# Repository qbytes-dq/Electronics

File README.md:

# Electronics

Electronic projects.

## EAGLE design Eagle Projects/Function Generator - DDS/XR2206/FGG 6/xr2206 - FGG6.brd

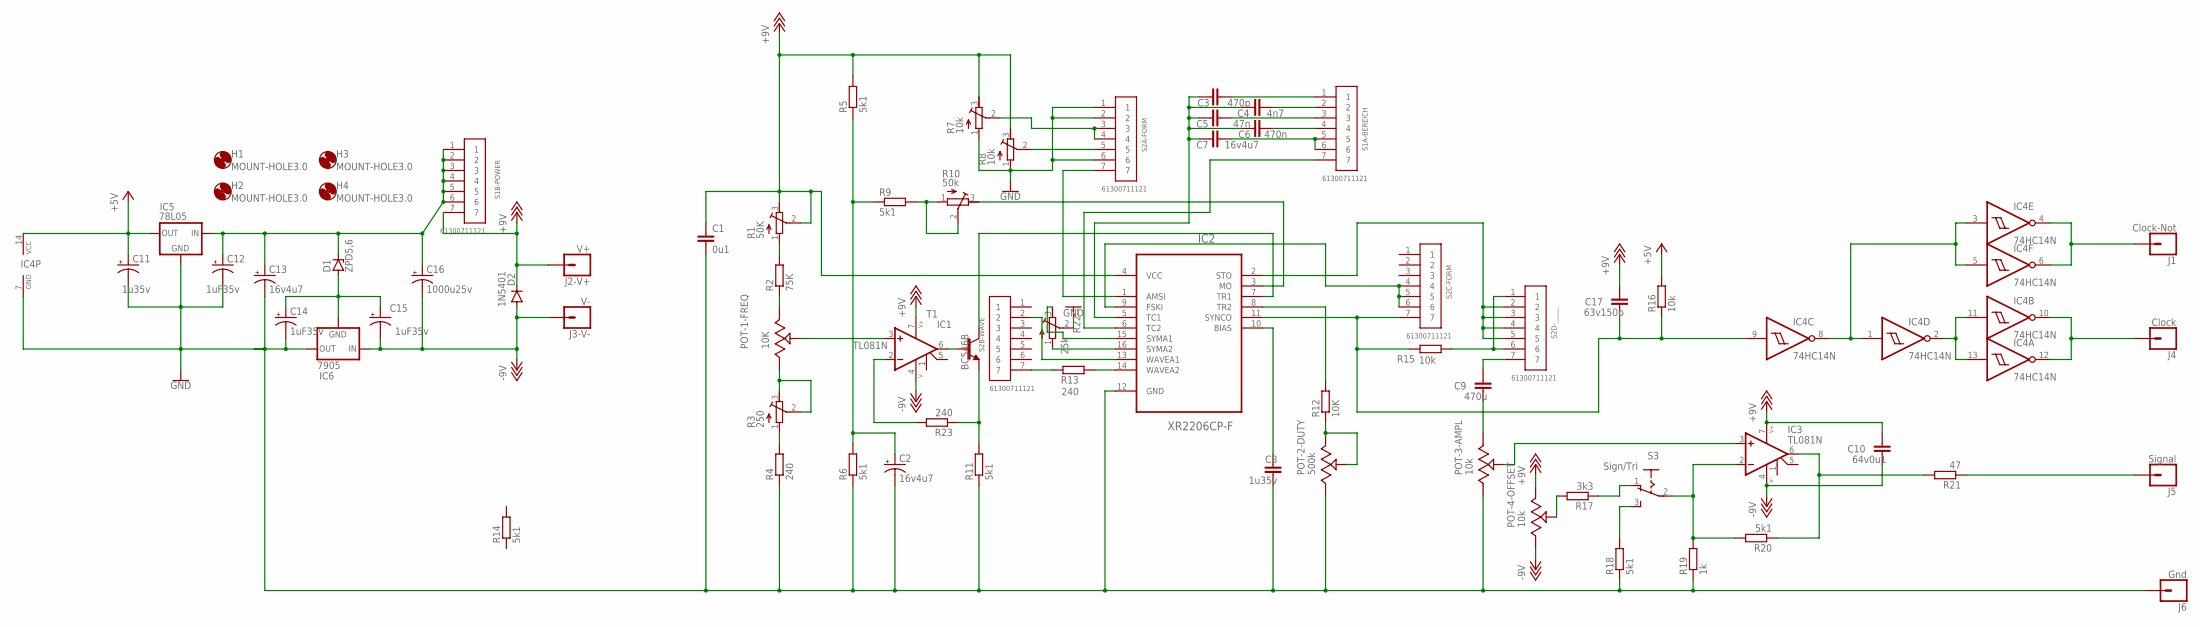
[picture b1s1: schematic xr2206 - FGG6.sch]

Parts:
C1: 0u1; CAP-PTH-10MM
C2: 16v4u7; CPOL-RADIAL-5MM-10MM-KIT
C3: 470p; CAP-PTH-10MM
C4: 4n7; CAP-PTH-10MM
C5: 47n; CAP-PTH-10MM
C6: 470n; CAP-PTH-10MM
C7: 16v4u7; CAP-PTH-10MM
C8: 1u35v; CAP-PTH-10MM
C9: 470u; CAP-PTH-10MM
C10: 64v0u1; CAP-PTH-10MM
C11: 1u35v; CPOL-RADIAL-2.5MM-5MM
C12, C14, C15: 1uF35v; CPOL-RADIAL-2.5MM-5MM
C13: 16v4u7; CPOL-RADIAL-2.5MM-5MM
C16: 1000u25v; CPOL-RADIAL-5MM-10MM-KIT
C17: 63v150p; CAP-PTH-10MM
D1: ZPD5,6; C1702-15
D2: 1N5401; DO201-15
H1, H2, H3, H4: MOUNT-HOLE3.0; 3,0
IC1, IC3: TL081N; DIL08
IC2: XR2206CP-F; DIP254P762X533-16
IC4: 74HC14N; DIL14
IC5: 78L05; 78XXL
IC6: 7905; 79XXL
J1: Clock-Not; 1X01
J2-V+: V+; 1X01
J3-V-: V-; 1X01
J4: Clock; 1X01
J5: Signal; 1X01
J6: Gnd; 1X01
POT-1-FREQ: 10K; 3310C-001-503L
POT-2-DUTY: 500k; 3310C-001-503L
POT-3-AMPL, POT-4-OFFSET: 10k; 3310C-001-503L
R1: 50K; RTRIM64W
R2: 75K; 0207/12
R3: 250; RTRIM64W
R4, R13: 240; 0207/7
R5, R6, R11, R14, R18, R20: 5k1; 0207/7
R7, R8: 10k; RTRIM64W
R9: 5k1; 0207/12
R10: 50k; RTRIM64W
R12: 10K; 0207/12
R15, R16: 10k; 0207/7
R17: 3k3; 0207/12
R19: 1k; 0207/7
R21: 47; 0207/7
R22---: 25k; RTRIM64W
R23: 240; 0207/12
S1A-BEREICH, S1B-POWER, S2A-FORM, S2B-WAVE, S2C-FORM, S2D-_____: 61300711121
S3: Sign/Tri; 255SB
T1: BC546B; TO92-EBC

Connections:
+5V: C11.1 (+), IC4.14 (VCC), IC5.OUT, R16.2
+18V: C1.1, C10.2, C17.2, D2.C, IC1.7 (V+), IC2.4 (VCC), IC3.7 (V+), J2-V+.1, POT-4-OFFSET.1, R1.2 (S), R1.3 (E), R5.2, R7.3 (E), R8.3 (E), S1B-POWER.7
-18V: C10.1, C15.2 (-), C16.-, D2.A, IC1.4 (V-), IC3.4 (V-), IC6.IN, J3-V-.1, POT-4-OFFSET.3
GND: C1.2, C2.-, C8.1, C11.2 (-), C12.2 (-), C13.2 (-), C14.2 (-), IC2.12 (GND), IC4.7 (GND), IC5.GND, IC6.OUT, J6.1, POT-2-DUTY.3, POT-3-AMPL.3, R4.1, R6.1, R7.1 (A), R8.1 (A), R11.1, R18.1, R19.1, R22---.2 (S), S2A-FORM.1, S2A-FORM.2, S2A-FORM.6
unnamed: R3.1 (A), R4.2
unnamed: POT-1-FREQ.3, R3.2 (S), R3.3 (E)
unnamed: POT-1-FREQ.1, R2.1
unnamed: R1.1 (A), R2.2
unnamed: C12.1 (+), C13.1 (+), C16.+, D1.C, IC5.IN, S1B-POWER.1, S1B-POWER.2, S1B-POWER.3, S1B-POWER.4, S1B-POWER.5, S1B-POWER.6
unnamed: C14.1 (+), C15.1 (+), D1.A, IC6.GND
unnamed: IC1.3 (+IN), POT-1-FREQ.2
unnamed: IC1.6 (OUT), T1.B
unnamed: IC1.2 (-IN), R23.2
unnamed: R11.2, R23.1, T1.E
unnamed: IC2.7 (TR1), T1.C
unnamed: C2.+, R5.1, R6.2, R9.1
unnamed: R9.2, R10.1 (A), R10.2 (S)
unnamed: IC2.3 (MO), R10.3 (E)
unnamed: IC2.8 (TR2), R12.2
unnamed: POT-2-DUTY.1, POT-2-DUTY.2, R12.1
unnamed: IC2.1 (AMSI), S2A-FORM.7
unnamed: R8.2 (S), S2A-FORM.5
unnamed: R7.2 (S), S2A-FORM.3, S2A-FORM.4
unnamed: IC2.13 (WAVEA1), S2B-WAVE.2
unnamed: R13.2, S2B-WAVE.7
unnamed: IC2.14 (WAVEA2), R13.1
unnamed: IC2.6 (TC2), S1A-BEREICH.7
unnamed: C3.1, C4.1, C5.1, C6.1, C7.1, IC2.5 (TC1)
unnamed: C3.2, S1A-BEREICH.1
unnamed: C4.2, S1A-BEREICH.2
unnamed: C6.2, S1A-BEREICH.4
unnamed: C5.2, S1A-BEREICH.3
unnamed: C7.2, S1A-BEREICH.5, S1A-BEREICH.6
unnamed: C8.2, IC2.10 (BIAS)
unnamed: IC2.9 (FSKI), S2C-FORM.4, S2C-FORM.5, S2C-FORM.6
unnamed: C17.1, IC2.11 (SYNCO), IC4.9 (I), R15.2, R16.1, S2C-FORM.7
unnamed: IC2.2 (STO), S2D-_____.2, S2D-_____.3, S2D-_____.4, S2D-_____.5
unnamed: IC4.1 (I), IC4.3 (I), IC4.5 (I), IC4.8 (O)
unnamed: IC4.2 (O), IC4.11 (I), IC4.13 (I)
unnamed: IC4.10 (O), IC4.12 (O), J4.1
unnamed: R15.1, S2D-_____.1, S2D-_____.6
unnamed: IC3.3 (+IN), POT-3-AMPL.2
unnamed: IC4.4 (O), IC4.6 (O), J1.1
unnamed: C9.2, S2D-_____.7
unnamed: C9.1, POT-3-AMPL.1
unnamed: POT-4-OFFSET.2, R17.2
unnamed: R17.1, S3.1 (O)
unnamed: IC3.2 (-IN), R19.2, R20.2, S3.2
unnamed: R18.2, S3.3 (S)
unnamed: IC3.6 (OUT), R20.1, R21.2
unnamed: J5.1, R21.1
unnamed: IC2.16 (SYMA2), R22---.1 (A)
unnamed: IC2.15 (SYMA1), R22---.3 (E)

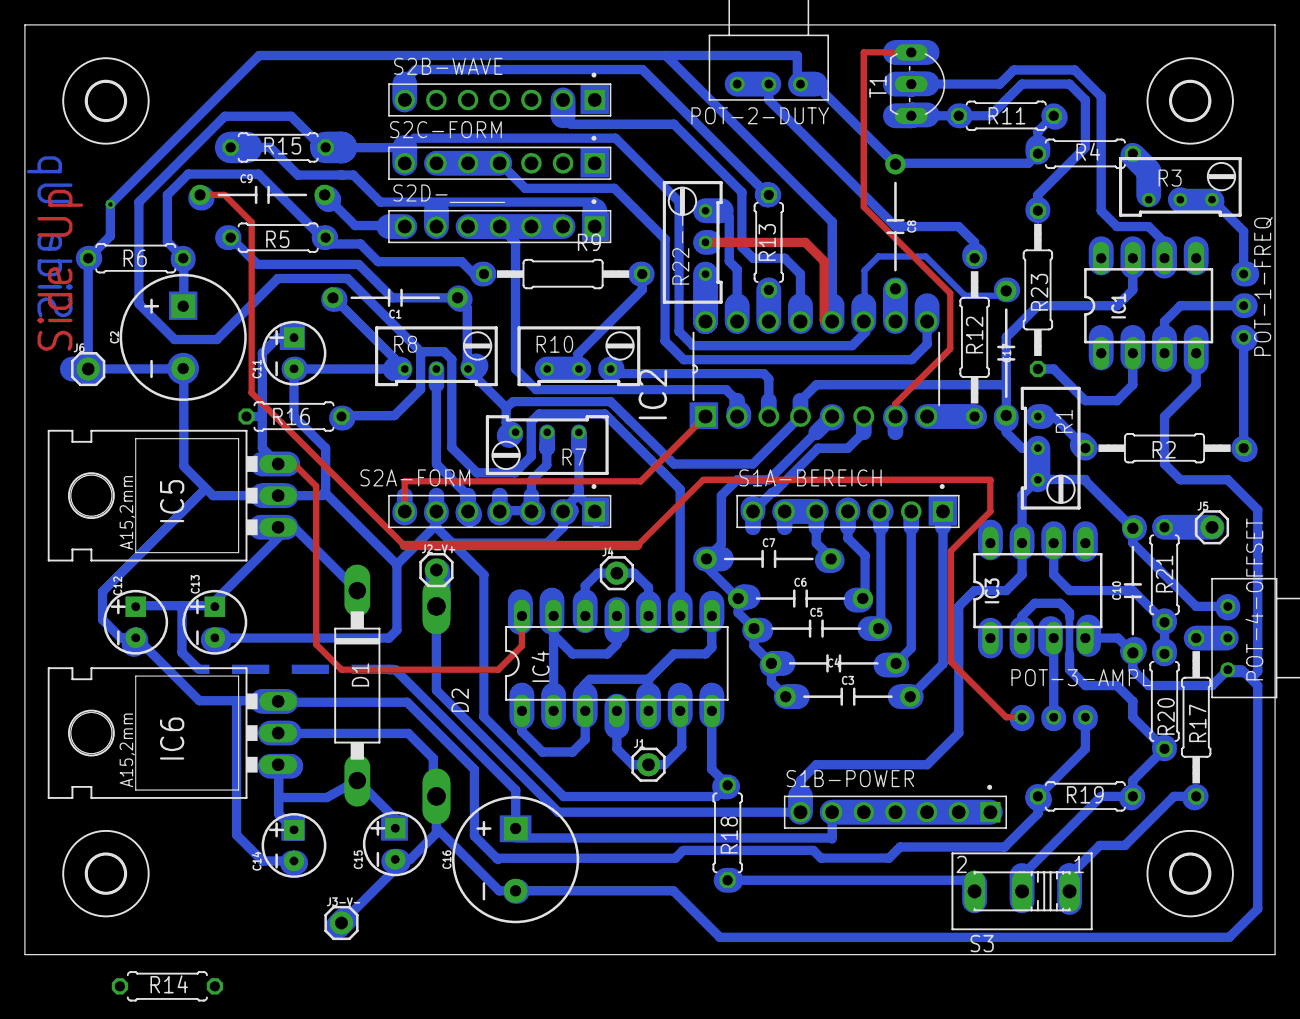
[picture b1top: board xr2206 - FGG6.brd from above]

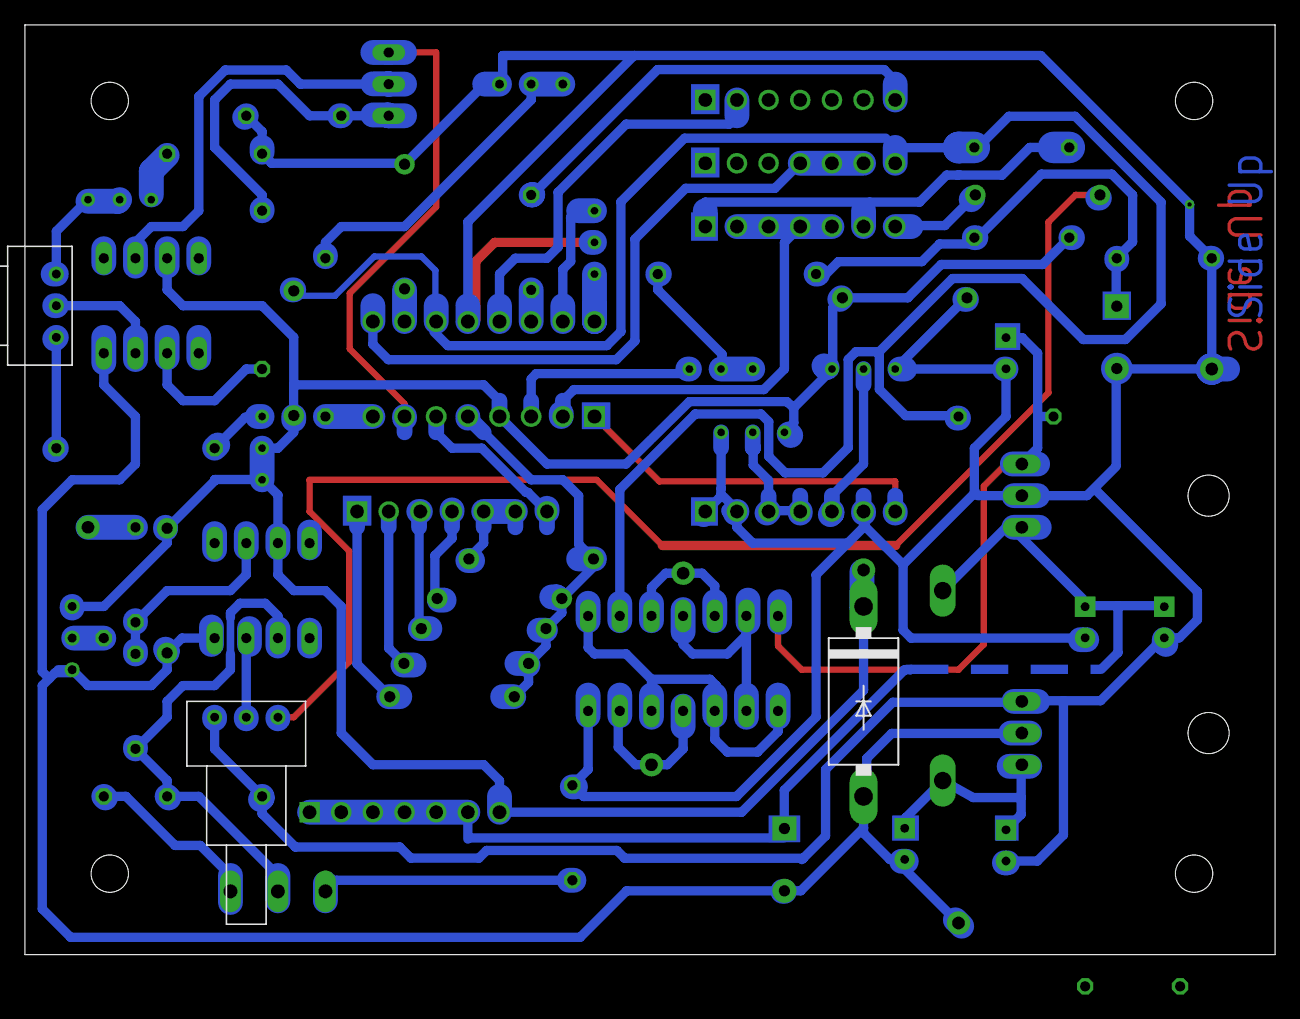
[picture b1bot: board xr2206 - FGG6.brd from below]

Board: 2 copper layers, 100.3 x 74.6 mm, 70 parts (3 on the bottom side), 53 nets.

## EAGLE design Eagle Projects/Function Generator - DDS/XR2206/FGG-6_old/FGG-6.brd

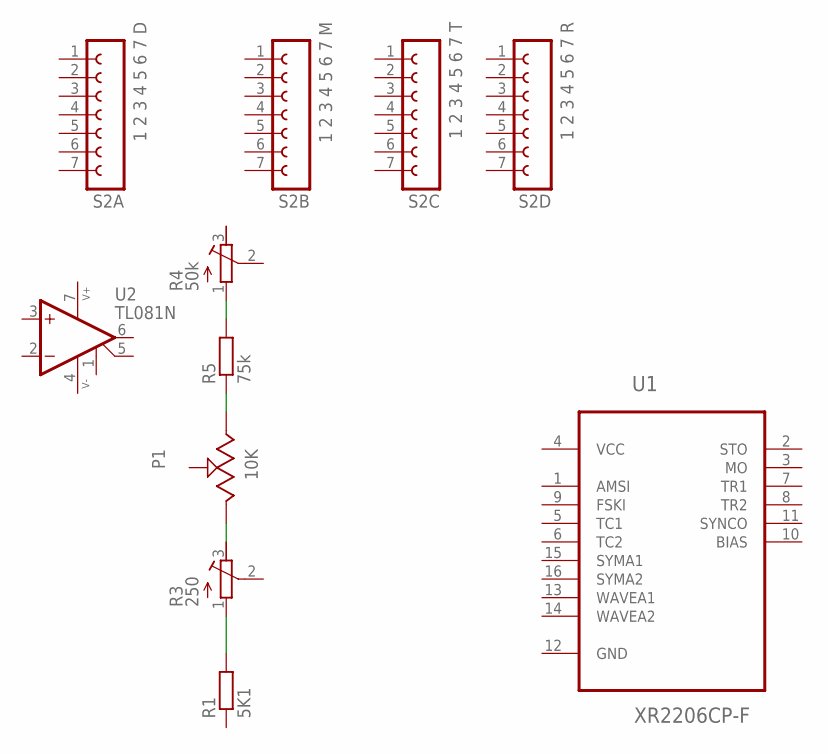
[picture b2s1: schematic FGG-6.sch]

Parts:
P1: 10K; 91A1A-B28-B15L-ND
R1: 5K1; 0207/10
R3: 250; RTRIM64W
R4: 50k; RTRIM64W
R5: 75k; 0207/10
S2A: 1 2 3 4 5 6 7 D; FE07
S2B: 1 2 3 4 5 6 7 M; FE07
S2C: 1 2 3 4 5 6 7 T; FE07
S2D: 1 2 3 4 5 6 7 R; FE07
U1: XR2206CP-F; DIP254P762X533-16
U2: TL081N; DIL08

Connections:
unnamed: R1.2, R3.1 (A)
unnamed: P1.1, R3.3 (E)
unnamed: P1.3, R5.1
unnamed: R4.1 (A), R5.2
V+: U2.7 (V+)
V-: U2.4 (V-)
VCC: U1.4 (VCC)

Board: 2 copper layers, 11 parts (0 on the bottom side), 4 nets, no tracks yet.

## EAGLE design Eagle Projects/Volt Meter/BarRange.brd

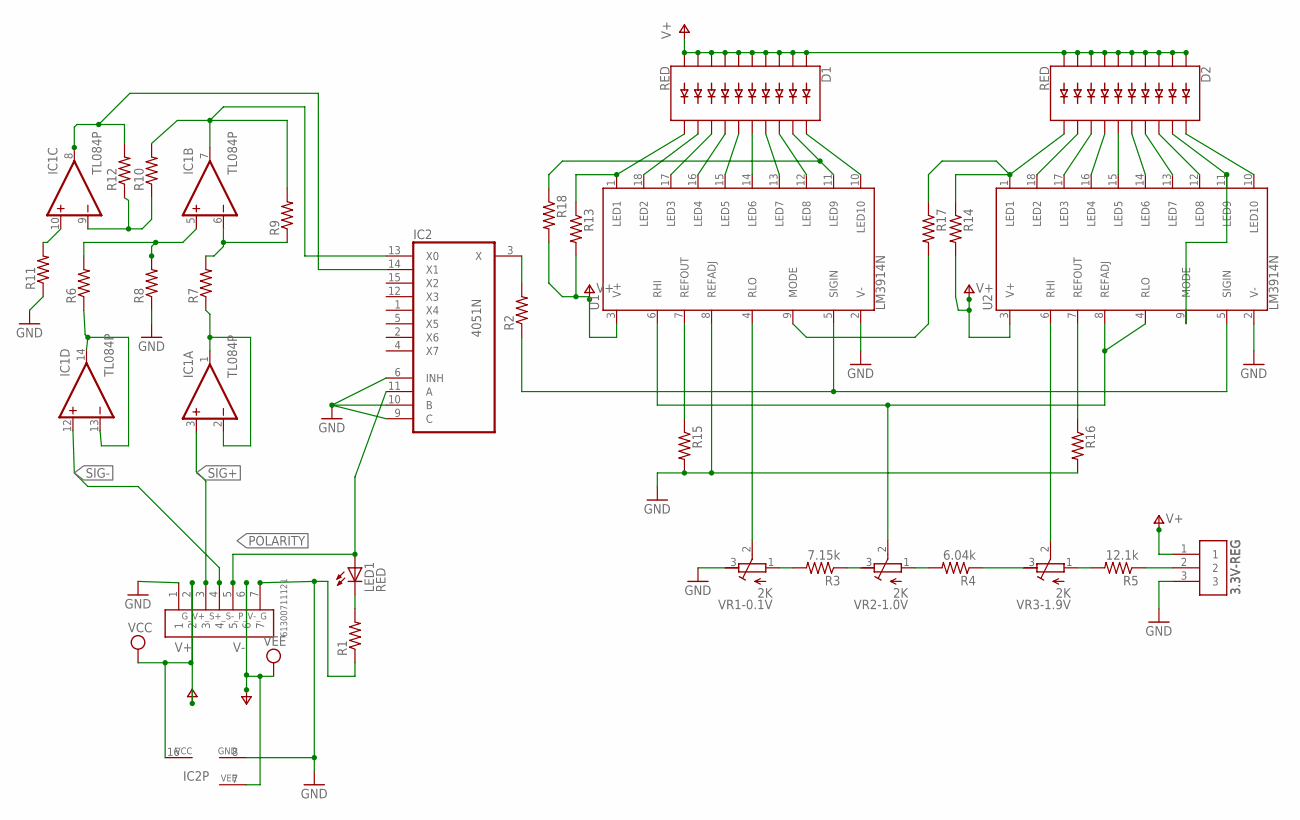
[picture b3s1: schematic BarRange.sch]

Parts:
3.3V-REG: 3.3V-REG; 61300311121
D1, D2: RED; LED_BARGRAPH_10
G_V+_S+_S-_P_V-_G: 61300711121
IC1: TL084P; DIL14
IC2: 4051N; DIL16
LED1: RED; LED5MM
R1, R2, R6, R7, R8, R9, R10, R11, R12, R13, R14, R15, R16, R17, R18: R-US_0204/7; 0204/7
R3: 7.15k; 0204/7
R4: 6.04k; 0204/7
R5: 12.1k; 0204/7
U1, U2: LM3914N; DIL18
VR1-0.1V, VR2-1.0V, VR3-1.9V: 2K; RTRIM3299W

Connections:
GND: 3.3V-REG.3, G_V+_S+_S-_P_V-_G.1, G_V+_S+_S-_P_V-_G.7, IC2.6 (INH), IC2.8 (GND), IC2.9 (C), IC2.10 (B), R1.1, R8.1, R11.1, R15.2, R16.2, U1.2 (V-), U1.8 (REFADJ), U2.2 (V-), VR1-0.1V.3 (E)
unnamed: IC1.5 (+IN), R6.2, R8.2
unnamed: D1.11 (C9), R13.1, U1.1 (LED1)
unnamed: D1.12 (C8), U1.18 (LED2)
unnamed: D1.13 (C7), U1.17 (LED3)
unnamed: D1.14 (C6), U1.16 (LED4)
unnamed: D1.15 (C5), U1.15 (LED5)
unnamed: D1.16 (C4), U1.14 (LED6)
unnamed: D1.17 (C3), U1.13 (LED7)
unnamed: D1.18 (C2), U1.12 (LED8)
unnamed: D1.19 (C1), R18.1, U1.11 (LED9)
unnamed: D1.20 (C), U1.10 (LED10)
unnamed: D2.11 (C9), R14.1, R17.1, U2.1 (LED1)
unnamed: D2.12 (C8), U2.18 (LED2)
unnamed: D2.13 (C7), U2.17 (LED3)
unnamed: D2.14 (C6), U2.16 (LED4)
unnamed: D2.15 (C5), U2.15 (LED5)
unnamed: D2.16 (C4), U2.14 (LED6)
unnamed: D2.17 (C3), U2.13 (LED7)
unnamed: D2.18 (C2), U2.12 (LED8)
unnamed: D2.19 (C1), U2.9 (MODE), U2.11 (LED9)
unnamed: D2.20 (C), U2.10 (LED10)
unnamed: LED1.K (C), R1.2
unnamed: IC2.3 (X), R2.2
unnamed: R2.1, U1.5 (SIGIN), U2.5 (SIGIN)
unnamed: R3.2, VR1-0.1V.1 (A)
unnamed: R3.1, VR2-1.0V.3 (E)
unnamed: R4.2, VR2-1.0V.1 (A)
unnamed: R4.1, VR3-1.9V.3 (E)
unnamed: R5.2, VR3-1.9V.1 (A)
unnamed: 3.3V-REG.2, R5.1
unnamed: U1.6 (RHI), U2.4 (RLO), U2.8 (REFADJ), VR2-1.0V.2 (S)
unnamed: IC1.1 (OUT), IC1.2 (-IN), R7.1
unnamed: U1.4 (RLO), VR1-0.1V.2 (S)
unnamed: IC1.13 (-IN), IC1.14 (OUT), R6.1
unnamed: IC1.6 (-IN), R7.2, R9.1
unnamed: IC1.7 (OUT), IC2.13 (X0), R9.2, R10.2
unnamed: IC1.10 (+IN), R11.2
unnamed: IC1.9 (-IN), R10.1, R12.1
unnamed: IC1.8 (OUT), IC2.14 (X1), R12.2
unnamed: U2.6 (RHI), VR3-1.9V.2 (S)
unnamed: R16.1, U2.7 (REFOUT)
unnamed: R15.1, U1.7 (REFOUT)
unnamed: R17.2, U1.9 (MODE)
POLARITY: G_V+_S+_S-_P_V-_G.5, IC2.11 (A), LED1.A
SIG+: G_V+_S+_S-_P_V-_G.3, IC1.3 (+IN)
SIG-: G_V+_S+_S-_P_V-_G.4, IC1.12 (+IN)
V+: 3.3V-REG.1, D1.1 (A), D1.2 (A1), D1.3 (A2), D1.4 (A3), D1.5 (A4), D1.6 (A5), D1.7 (A6), D1.8 (A7), D1.9 (A8), D1.10 (A9), D2.1 (A), D2.2 (A1), D2.3 (A2), D2.4 (A3), D2.5 (A4), D2.6 (A5), D2.7 (A6), D2.8 (A7), D2.9 (A8), D2.10 (A9), G_V+_S+_S-_P_V-_G.2, IC1.4 (V+), IC2.16 (VCC), R13.2, R14.2, R18.2, U1.3 (V+), U2.3 (V+)
V-: G_V+_S+_S-_P_V-_G.6, IC1.11 (V-), IC2.7 (VEE)

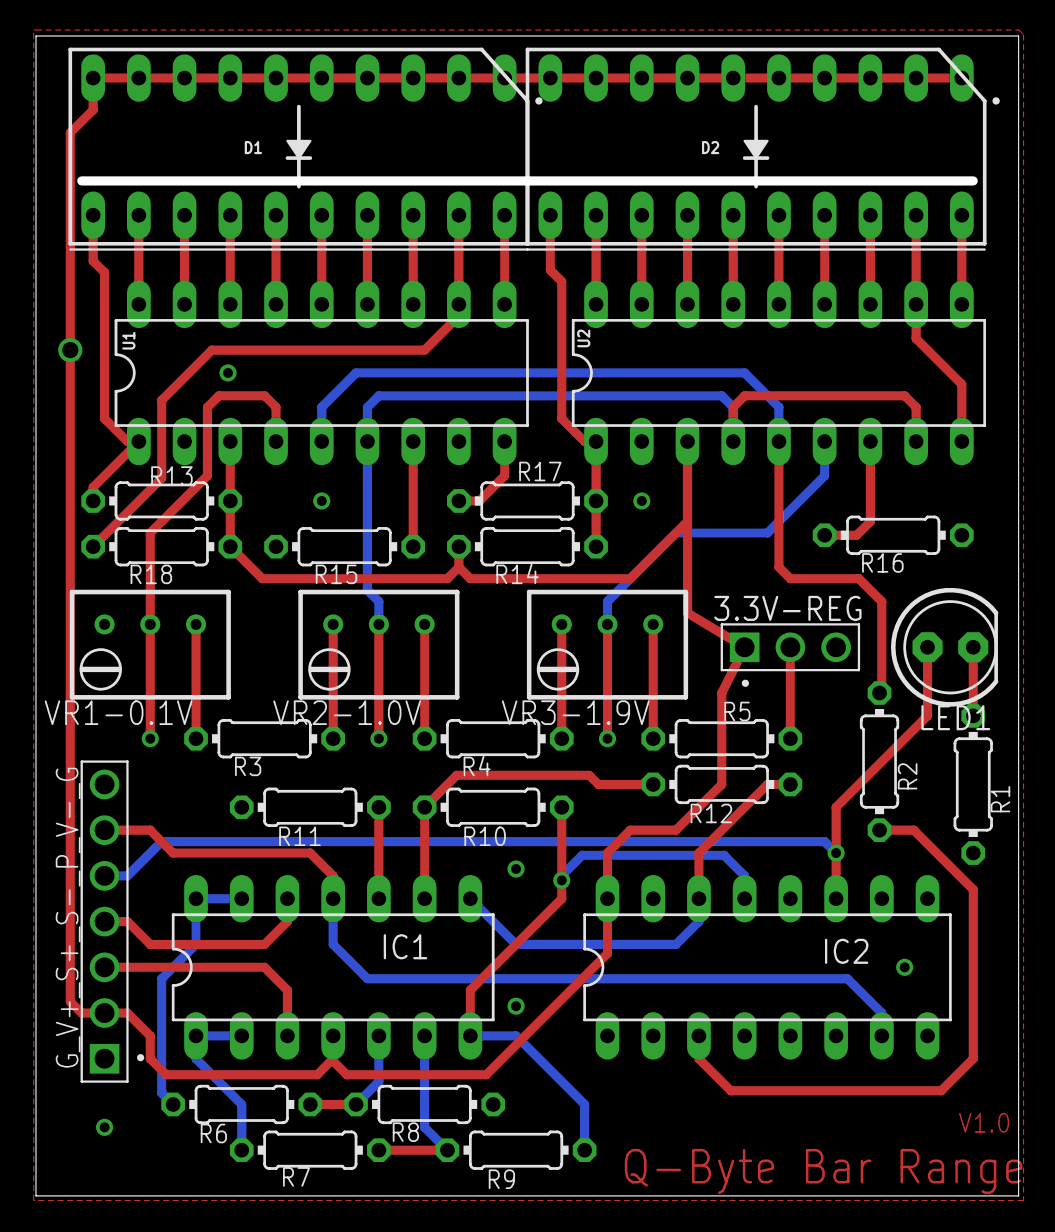
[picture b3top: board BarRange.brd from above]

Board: 2 copper layers, 54.6 x 64.4 mm, 30 parts (0 on the bottom side), 49 nets.

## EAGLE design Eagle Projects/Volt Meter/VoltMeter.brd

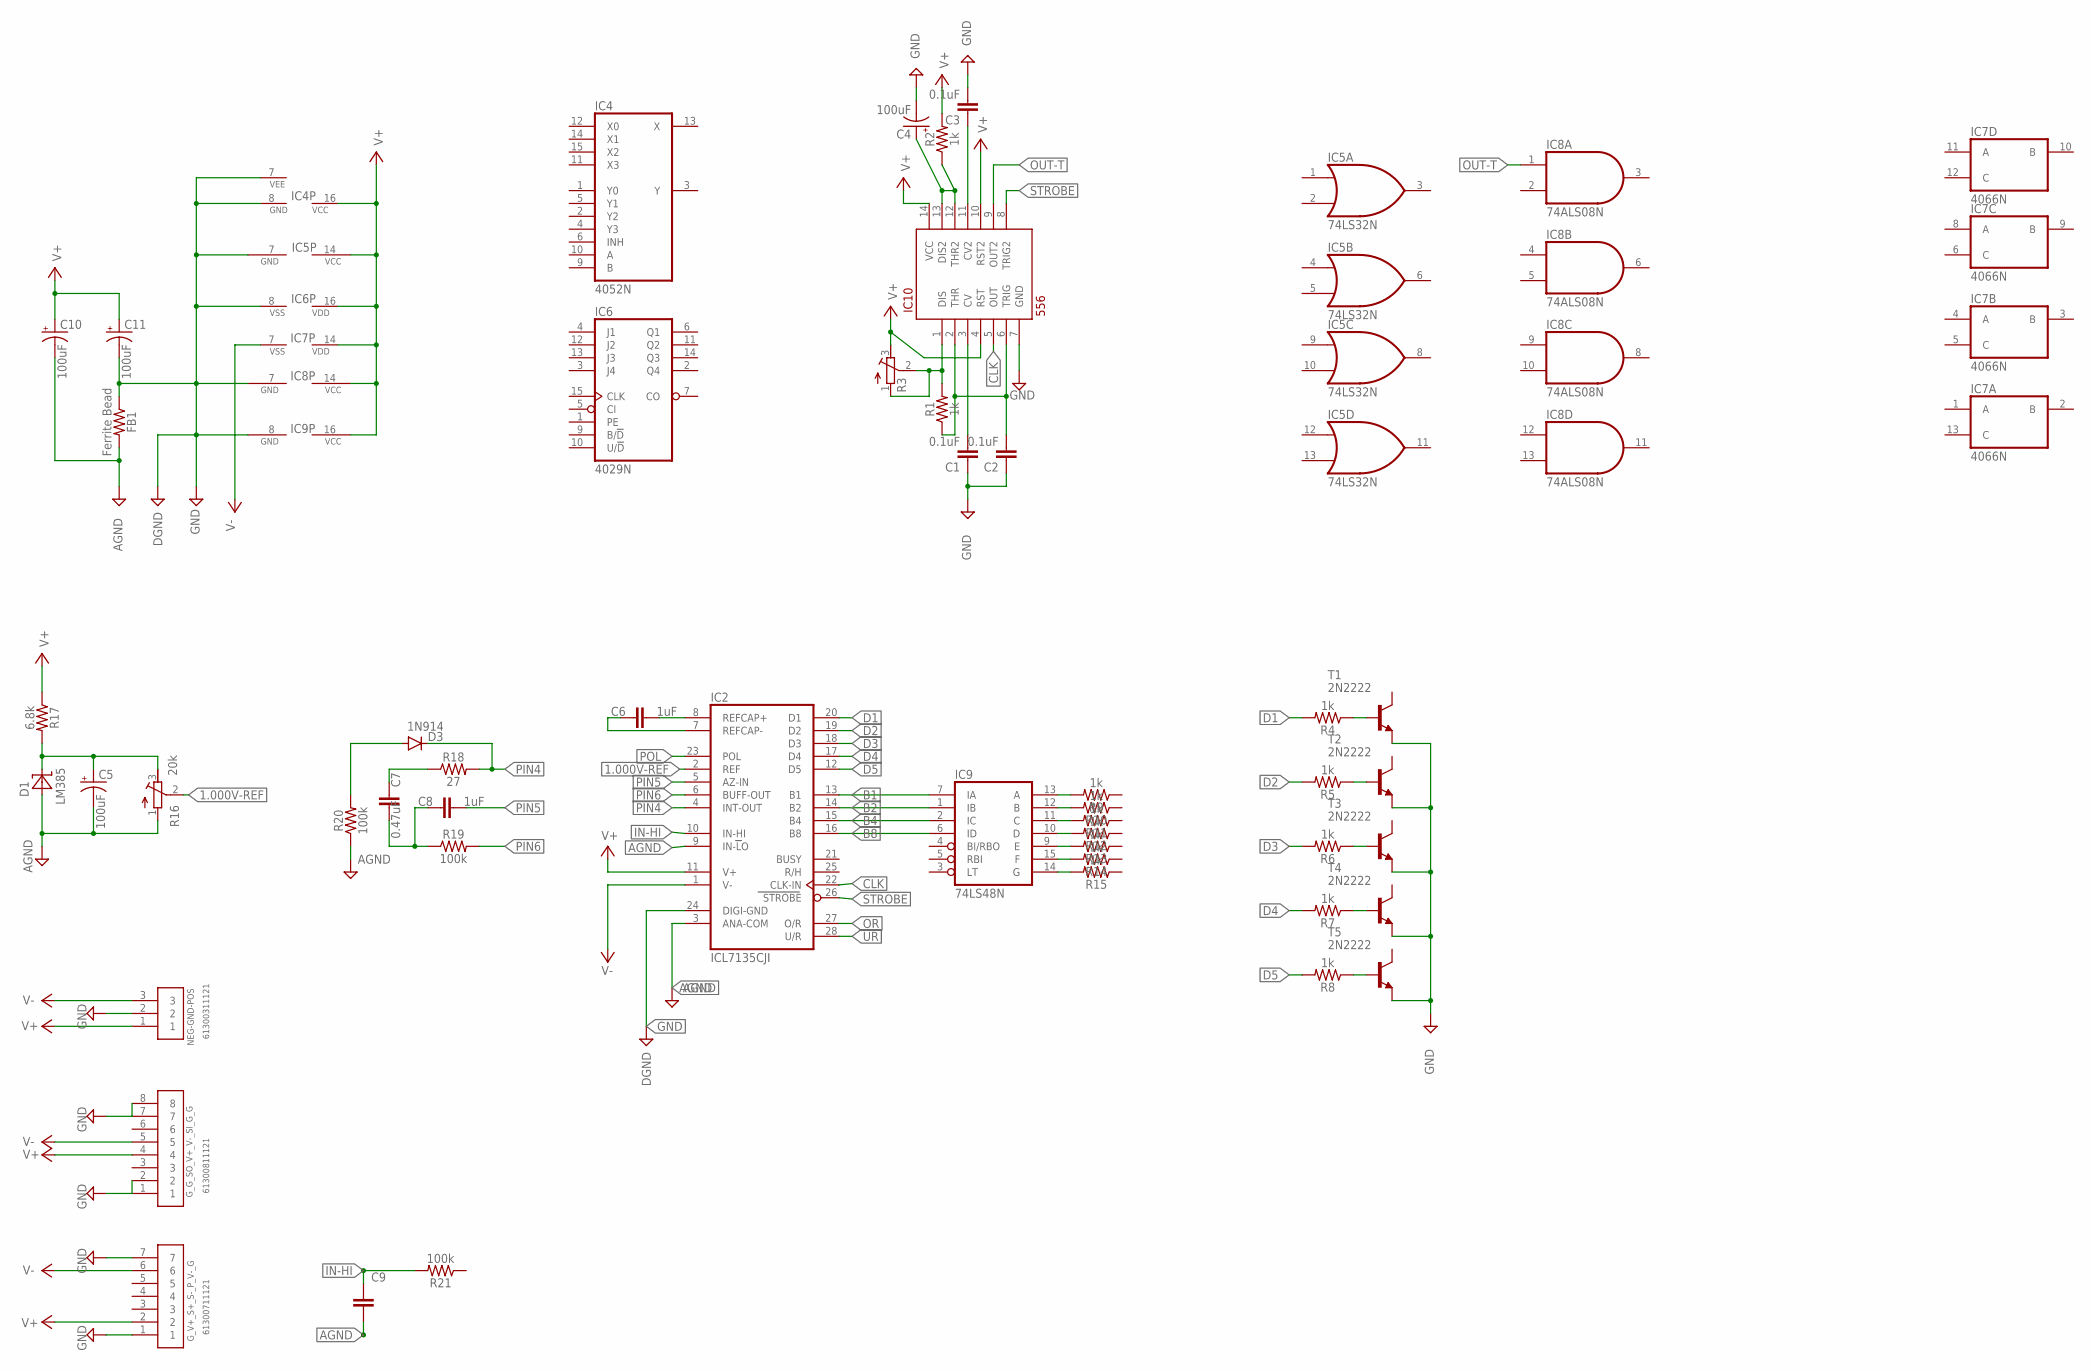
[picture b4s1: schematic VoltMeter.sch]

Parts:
C1, C2, C3: 0.1uF; CAP-PTH-SMALL-KIT
C4, C5, C10, C11: 100uF; CPOL-RADIAL-2.5MM-6.5MM
C6, C8: 1uF; CAP-PTH-SMALL-KIT
C7: 0.47uF; CAP-PTH-SMALL-KIT
C9: 0.1uF; C5B2.5
D1: LM385; TO-92
D3: 1N914; DO35-7
FB1: Ferrite Bead; AXIAL-0.3
G_G_SO_V+_V-_SI_G_G: 61300811121
G_V+_S+_S-_P_V-_G: 61300711121
IC2: ICL7135CJI; DIL28-6
IC4: 4052N; DIL16
IC5: 74LS32N; DIL14
IC6: 4029N; DIL16
IC7: 4066N; DIL14
IC8: 74ALS08N; DIL14
IC9: 74LS48N; DIL16
IC10: 556; DIP14
NEG-GND-POS: 61300311121
R1, R2, R4, R5, R6, R7, R8, R9, R10, R11, R12, R13, R14, R15: 1k; AXIAL-0.3
R3: R-TRIMM3299W; RTRIM3299W
R16: 20k; RTRIM3299W
R17: 6.8k; AXIAL-0.3
R18: 27; AXIAL-0.3
R19, R20, R21: 100k; AXIAL-0.3
T1, T2, T3, T4, T5: 2N2222; TO92-EBC-OVAL

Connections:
1.000V-REF: IC2.2 (REF), R16.2 (S)
AGND: C5.2 (-), C9.2, C10.2 (-), D1.+, FB1.P$2 (2), IC2.3 (ANA-COM), IC2.9 (IN-LO), R16.1 (A), R20.P$1 (1)
B1: IC2.13 (B1), IC9.7 (IA)
B2: IC2.14 (B2), IC9.1 (IB)
B4: IC2.15 (B4), IC9.2 (IC)
B8: IC2.16 (B8), IC9.6 (ID)
CLK: IC2.22 (CLK-IN), IC10.5 (OUT)
D1: IC2.20 (D1), R4.P$2 (2)
D2: IC2.19 (D2), R5.P$2 (2)
D3: IC2.18 (D3), R6.P$2 (2)
D4: IC2.17 (D4), R7.P$2 (2)
D5: IC2.12 (D5), R8.P$2 (2)
GND: C1.1, C2.1, C3.2, C4.2 (-), C11.2 (-), FB1.P$1 (1), G_G_SO_V+_V-_SI_G_G.1, G_G_SO_V+_V-_SI_G_G.2, G_G_SO_V+_V-_SI_G_G.7, G_G_SO_V+_V-_SI_G_G.8, G_V+_S+_S-_P_V-_G.1, G_V+_S+_S-_P_V-_G.7, IC2.24 (DIGI-GND), IC4.7 (VEE), IC4.8 (GND), IC5.7 (GND), IC6.8 (VSS), IC8.7 (GND), IC9.8 (GND), IC10.7 (GND), NEG-GND-POS.2, T1.E, T2.E, T3.E, T4.E, T5.E
IN-HI: C9.1, IC2.10 (IN-HI), R21.P$2 (2)
unnamed: C2.2, IC10.2 (THR), IC10.6 (TRIG), R1.P$1 (1)
unnamed: IC10.1 (DIS), R1.P$2 (2), R3.1 (A), R3.2 (S)
unnamed: C4.1 (+), IC10.12 (THR2), IC10.13 (DIS2), R2.P$1 (1)
unnamed: C1.2, IC10.3 (CV)
unnamed: C3.1, IC10.11 (CV2)
unnamed: R4.P$1 (1), T1.B
unnamed: R5.P$1 (1), T2.B
unnamed: R6.P$1 (1), T3.B
unnamed: R7.P$1 (1), T4.B
unnamed: R8.P$1 (1), T5.B
unnamed: IC9.13 (A), R9.P$2 (2)
unnamed: IC9.12 (B), R10.P$2 (2)
unnamed: IC9.11 (C), R11.P$2 (2)
unnamed: IC9.10 (D), R12.P$2 (2)
unnamed: IC9.9 (E), R13.P$2 (2)
unnamed: IC9.15 (F), R14.P$2 (2)
unnamed: IC9.14 (G), R15.P$2 (2)
unnamed: C6.2, IC2.8 (REFCAP+)
unnamed: D3.A, R20.P$2 (2)
unnamed: C7.1, R18.P$1 (1)
unnamed: C7.2, C8.1, R19.P$1 (1)
unnamed: C6.1, IC2.7 (REFCAP-)
OR: IC2.27 (O/R)
OUT-T: IC8.1 (I0), IC10.9 (OUT2)
PIN4: D3.C, IC2.4 (INT-OUT), R18.P$2 (2)
PIN5: C8.2, IC2.5 (AZ-IN)
PIN6: IC2.6 (BUFF-OUT), R19.P$2 (2)
POL: IC2.23 (POL)
STROBE: IC2.26 (STROBE), IC10.8 (TRIG2)
UR: IC2.28 (U/R)
V+: C10.1 (+), C11.1 (+), G_G_SO_V+_V-_SI_G_G.4, G_V+_S+_S-_P_V-_G.2, IC2.11 (V+), IC4.16 (VCC), IC5.14 (VCC), IC6.16 (VDD), IC7.14 (VDD), IC8.14 (VCC), IC9.16 (VCC), IC10.4 (RST), IC10.10 (RST2), IC10.14 (VCC), NEG-GND-POS.1, R2.P$2 (2), R3.3 (E), R17.P$1 (1)
V-: G_G_SO_V+_V-_SI_G_G.5, G_V+_S+_S-_P_V-_G.6, IC2.1 (V-), IC7.7 (VSS), NEG-GND-POS.3
VREF-1.0V: C5.1 (+), D1.-, R16.3 (E), R17.P$2 (2)

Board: 2 copper layers, 51 parts (1 on the bottom side), 44 nets, no tracks yet.

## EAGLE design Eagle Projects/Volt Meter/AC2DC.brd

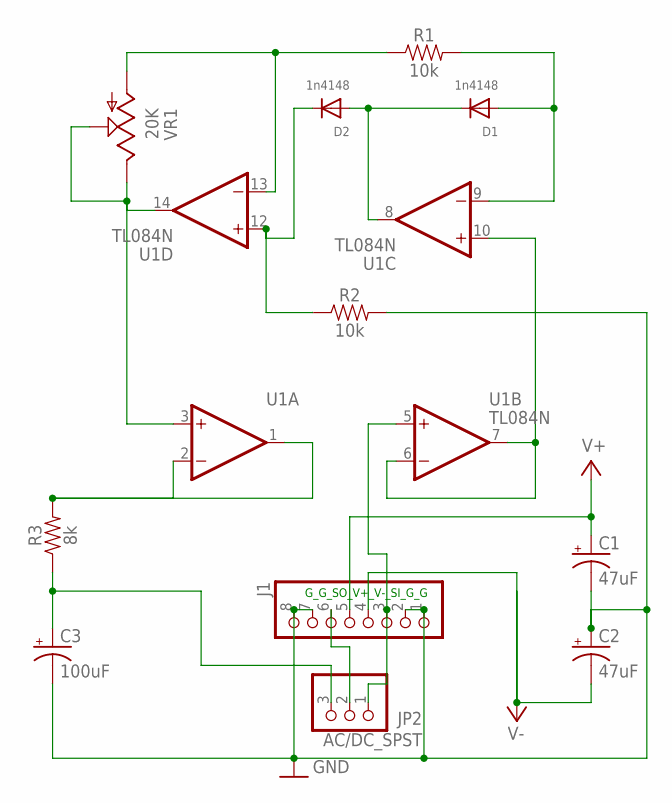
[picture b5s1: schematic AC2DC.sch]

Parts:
AC/DC_SPST: JP2; 1X03
C1, C2: 47uF; E5-4
C3: 100uF; E5-4
D1, D2: 1n4148; DO-1N4148
G_G_SO_V+_V-_SI_G_G: J1; 1X08-BIG
R1, R2: 10k; AXIAL-0.3
R3: 8k; AXIAL-0.3
U1: TL084N; DIL14
VR1: 20K; S64W

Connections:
GND: C1.-, C2.+, C3.-, G_G_SO_V+_V-_SI_G_G.1, G_G_SO_V+_V-_SI_G_G.2, G_G_SO_V+_V-_SI_G_G.7, G_G_SO_V+_V-_SI_G_G.8, R2.P$2 (2)
unnamed: AC/DC_SPST.3, C3.+, R3.P$1 (1)
unnamed: U1.6 (-IN), U1.7 (OUT), U1.10 (+IN)
unnamed: R3.P$2 (2), U1.1 (OUT), U1.2 (-IN)
unnamed: R1.P$1 (1), U1.13 (-IN), VR1.A
unnamed: U1.3 (+IN), U1.14 (OUT), VR1.E, VR1.S
unnamed: AC/DC_SPST.1, G_G_SO_V+_V-_SI_G_G.3, U1.5 (+IN)
unnamed: D1.C, D2.A, U1.8 (OUT)
unnamed: D1.A, R1.P$2 (2), U1.9 (-IN)
unnamed: AC/DC_SPST.2, G_G_SO_V+_V-_SI_G_G.6
unnamed: D2.C, R2.P$1 (1), U1.12 (+IN)
V+: C1.+, G_G_SO_V+_V-_SI_G_G.5, U1.4 (V+)
V-: C2.-, G_G_SO_V+_V-_SI_G_G.4, U1.11 (V-)

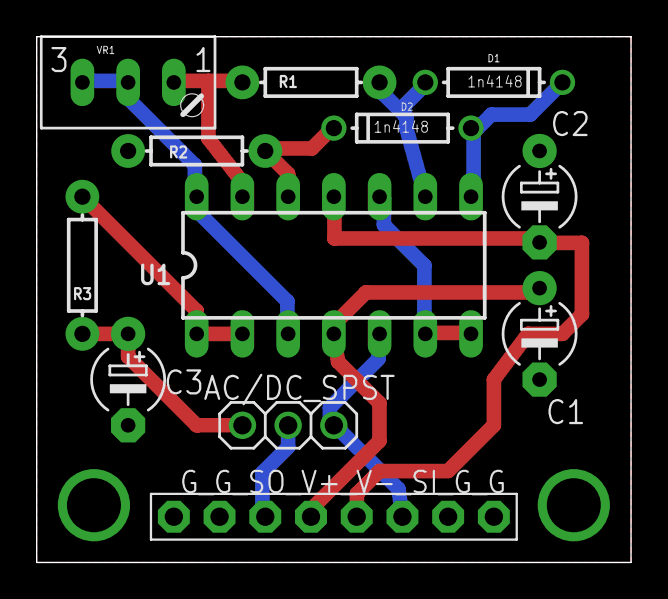
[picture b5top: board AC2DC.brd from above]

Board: 2 copper layers, 33.0 x 29.2 mm, 12 parts (0 on the bottom side), 13 nets.

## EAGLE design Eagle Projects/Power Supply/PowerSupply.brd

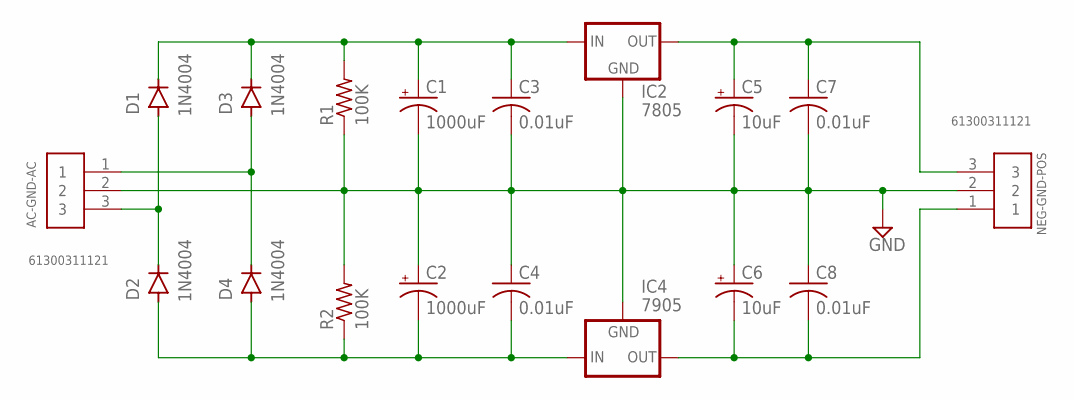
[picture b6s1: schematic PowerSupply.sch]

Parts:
AC-GND-AC: 61300311121
C1, C2: 1000uF; E3,5-8
C3, C4, C7, C8: 0.01uF; C050-025X075
C5, C6: 10uF; E2,5-6
D1, D2, D3, D4: 1N4004; DO-41
IC2: 7805; 78XXS
IC4: 7905; 79XXS
NEG-GND-POS: 61300311121
R1, R2: 100K; 0411/12

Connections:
AC1: AC-GND-AC.1, D3.A, D4.C
AC2: AC-GND-AC.3, D1.A, D2.C
GND: AC-GND-AC.2, C1.-, C2.+, C3.2, C4.1, C5.-, C6.+, C7.2, C8.1, IC2.GND, IC4.GND, NEG-GND-POS.2, R1.1, R2.2
unnamed: C6.-, C8.2, IC4.OUT, NEG-GND-POS.1
unnamed: C5.+, C7.1, IC2.OUT, NEG-GND-POS.3
unnamed: C1.+, C3.1, D1.C, D3.C, IC2.IN, R1.2
unnamed: C2.-, C4.2, D2.A, D4.A, IC4.IN, R2.1

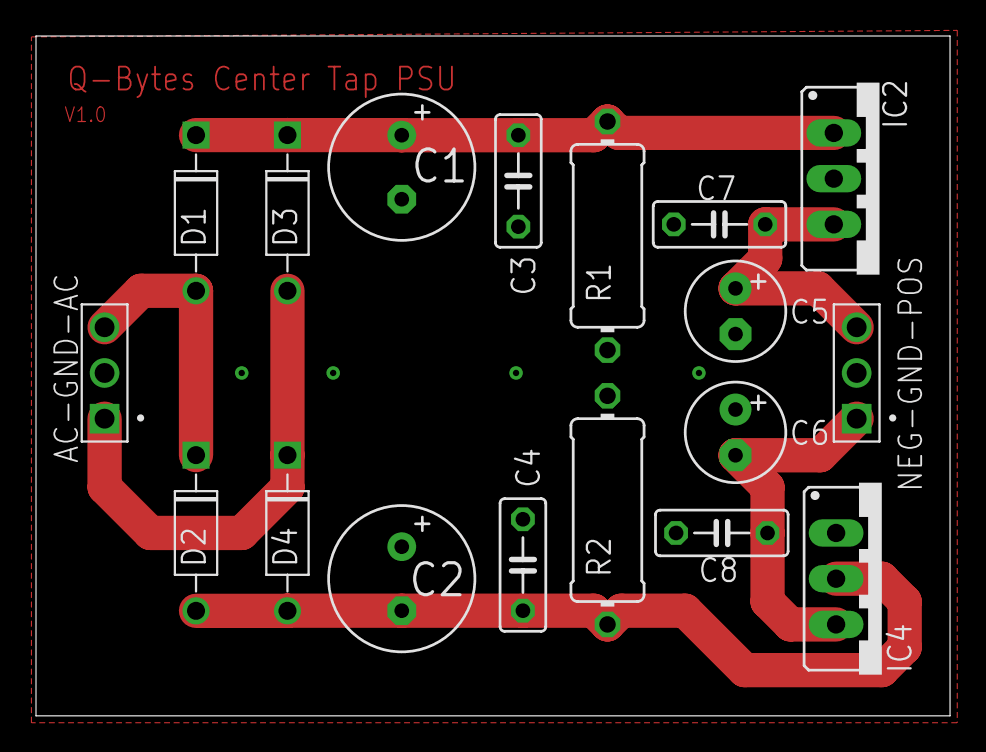
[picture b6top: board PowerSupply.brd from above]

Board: 2 copper layers, 50.8 x 37.8 mm, 18 parts (0 on the bottom side), 7 nets.

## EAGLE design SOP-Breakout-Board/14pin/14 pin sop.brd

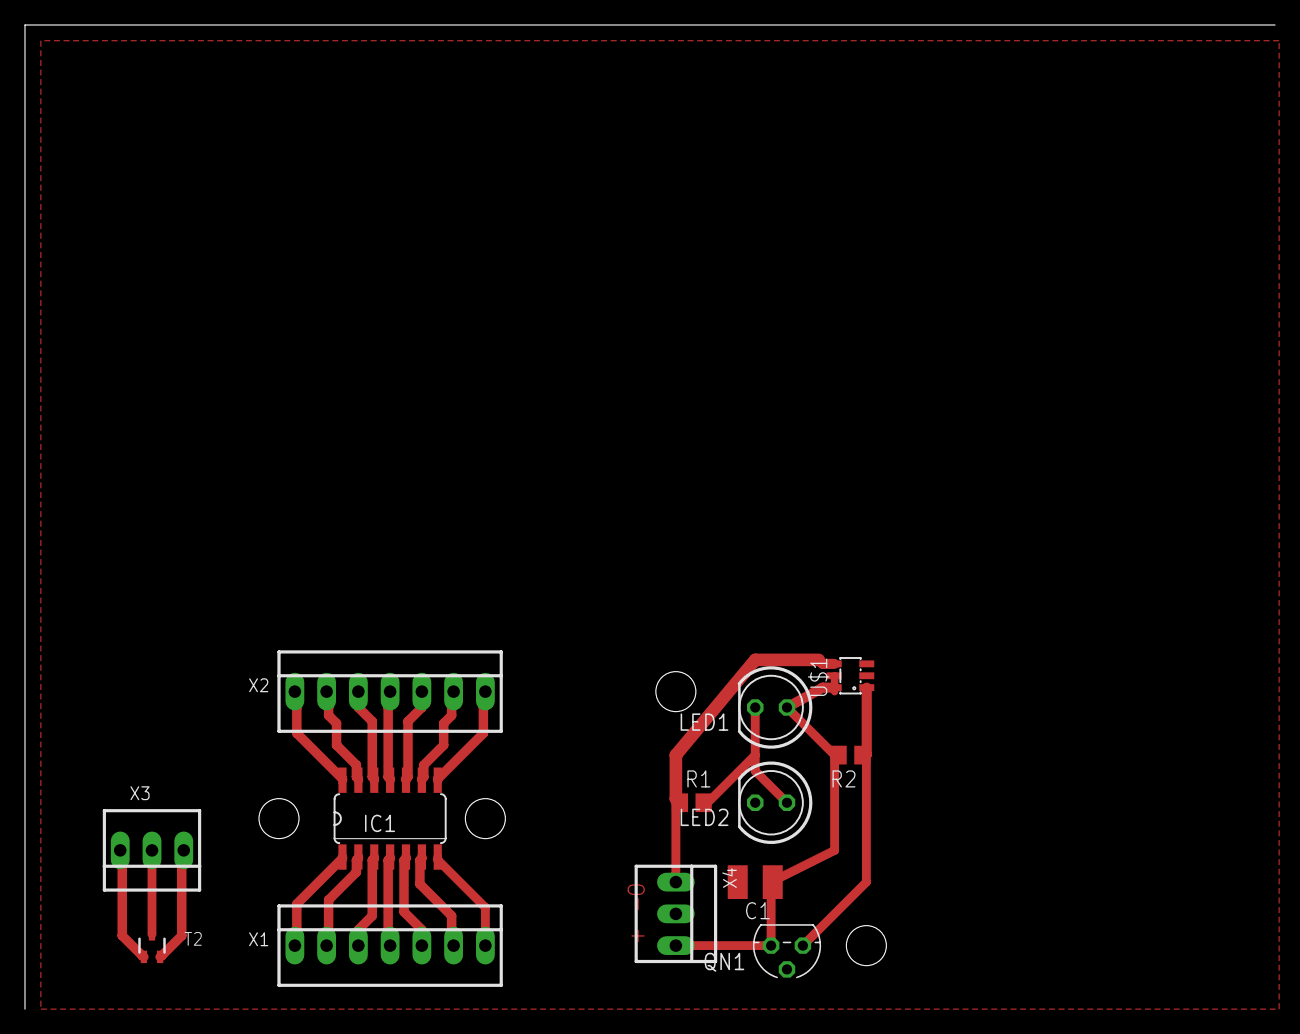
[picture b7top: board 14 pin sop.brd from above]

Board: 2 copper layers, 100.0 x 78.7 mm, 13 parts (0 on the bottom side), 21 nets.

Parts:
C1: 100nF; C1210
IC1: 74AS04D; SO14
LED1: On; LED5MM
LED2: Off; LED5MM
QN1: 2N3904; TO92
R1: 330; R0805
R2: 10k; R0805
T2: BFR91; SOT323
U$1: LT3426; SOT23-6
X1, X2: 22-23-2071
X3, X4: 22-23-2031

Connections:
GND: C1.2, IC1.7, LED2.K, QN1.2, U$1.2, U$1.3, X1.7, X4.2
unnamed: IC1.1, X1.1
unnamed: IC1.2, X1.2
unnamed: IC1.3, X1.3
unnamed: IC1.4, X1.4
unnamed: IC1.5, X1.5
unnamed: IC1.6, X1.6
unnamed: IC1.8, X2.7
unnamed: IC1.9, X2.6
unnamed: IC1.10, X2.5
unnamed: IC1.11, X2.4
unnamed: IC1.12, X2.3
unnamed: IC1.13, X2.2
unnamed: C1.1, LED1.A, QN1.1, R2.2, U$1.5, U$1.6, X4.3
unnamed: T2.2, X3.3
unnamed: T2.3, X3.1
unnamed: T2.1, X3.2
unnamed: QN1.3, R2.1, U$1.1
unnamed: R1.1, U$1.4, X4.1
unnamed: LED1.K, LED2.A, R1.2
VCC: IC1.14, X2.1

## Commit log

2015-09-21 :lollipop: Added .gitattributes
2015-09-21 Initial Check in
    Electronics projects
2015-09-23 Move clock to Timer2
    Move clock to Timer2
2015-09-24 Serial RX/TX
    Serial communication with PIC2 UART
2016-11-13 Lost Changes
    Merge code from old GitHub and Computer.
2016-11-13 Still syncing to GIT
    Still syncing to GIT
2016-11-13 Still finding code
    Still finding code
2019-07-11 Eagle Projects
2019-07-11 Organize
2019-10-17 Add XTL curcuit
2019-10-22 move from SVN
2020-04-09 FGG 6 schematic and Board
2021-01-02 Adding Coil winder
2021-02-08 Toroid coil winder check-in
2021-02-11 Update Stepper_w-ULN2003.ino
    Added initial logic for calculations
2021-02-11 Update Stepper_w-ULN2003.ino
    completed steps to load toroid
    Need to complete stepper motot code while loading.
2021-02-11 Update Stepper_w-ULN2003.ino
    Need to complete the stepper code
2021-02-12 Update Stepper_w-ULN2003.ino
    Working on ID Step Size
2021-02-13 Update Stepper_w-ULN2003.ino
    Making progress on the Load Toroid
2021-02-14 Update Stepper_w-ULN2003.ino
    Ready a thread test.
2021-02-14 Update Stepper_w-ULN2003.ino
    Ready for winding
2021-02-14 Update Stepper_w-ULN2003.ino
    Thread worked well.

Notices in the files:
parts and their libraries:
op-amp: Copyright (C) 2006 by Bob Starr
SparkFun-Capacitors: Licensing: Creative Commons ShareAlike 4.0 International - https://creativecommons.org/licenses/by-sa/4.0
